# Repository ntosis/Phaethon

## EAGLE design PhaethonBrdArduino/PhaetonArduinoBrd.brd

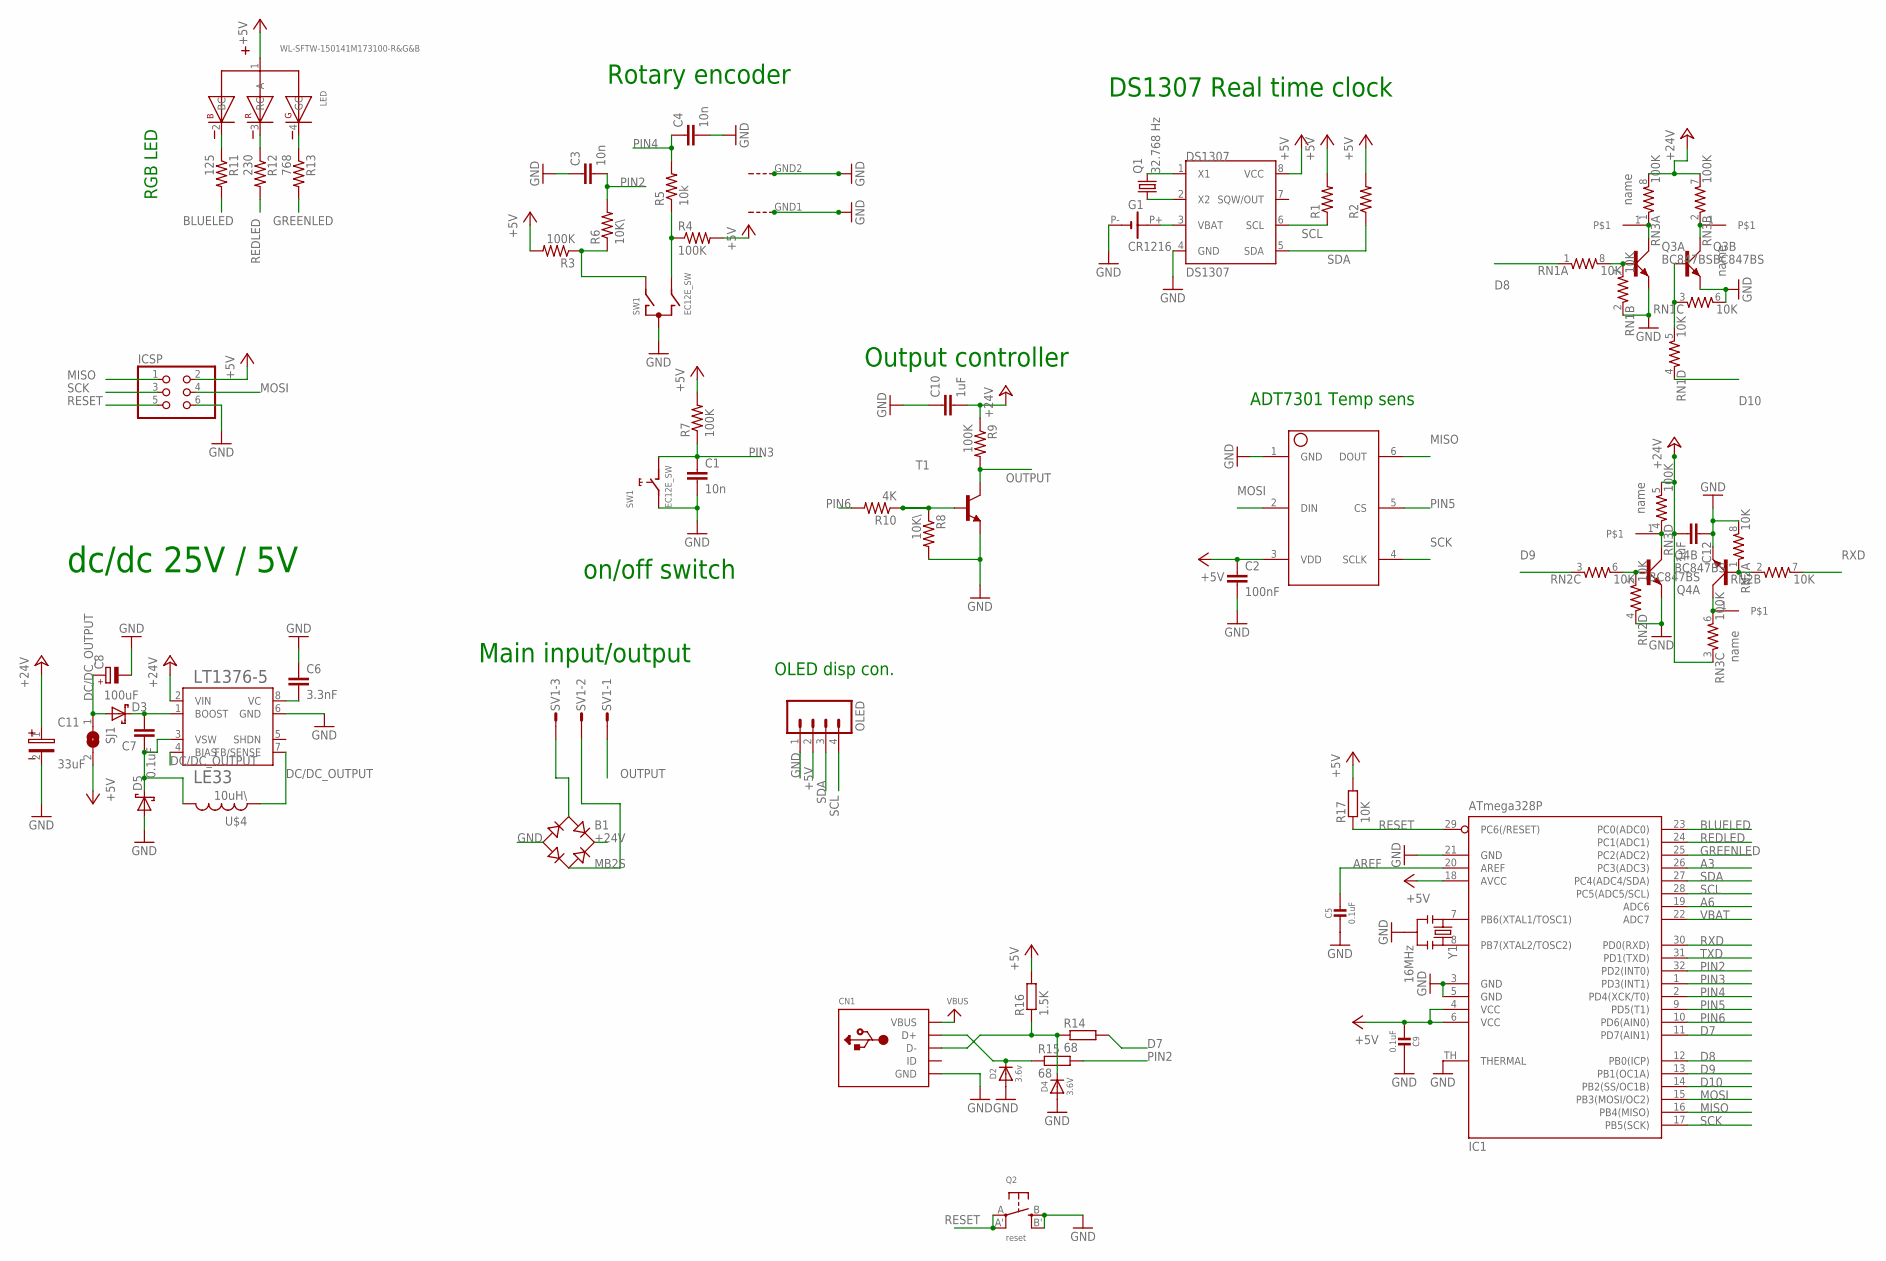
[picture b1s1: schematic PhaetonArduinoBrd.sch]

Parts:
ADT: ADT7301; SOT23-6
B1: MB2S; SOIC-4
C1, C3, C4: 10n; C0504
C2: 100nF; C0504
C5, C9: 0.1uF; _0805MP
C6: 3.3nF; C0504
C7: 0.1uF; C0504
C8: 100uF; CT7343
C10, C12: 1uF; C0402
C11: 33uF; 3X1.6X1.4(BXCXA)
CN1: USBMINIB; USB-MINIB
D2: 3.6v; SOD-323
D3, D5: SCHOTTKY; DO214
D4: 3.6V; SOD-323
DS1307: DS1307; SOIC-8
G1: CR1216; SMTU1225-LF
IC1: ATmega328P; MLF32-TH
ICSP: PINHD-2X3; 2X03
LED: WL-SFTW-150141M173100-R&G&B; 3528-COMMON-ANODE
LT1376-5: LE33; SO08
OLED: M04; 04P
OUTPUT2: MINICONECTOR; SMD
Q1: 32.768 Hz; TC26V
Q2: reset; BTN_KMR2_4.6X2.8
Q3, Q4: BC847BS; SOT363_PHILIPS
R1, R2: RESISTOR; 0805
R3, R4, R7, R9: 100K; 0805
R5: 10k; 0805
R6, R8: 10K\; 0805
R10: 4K; 0805
R11: 125; 0805
R12: 230; 0805
R13: 768; 0805
R14, R15: 68; R0603
R16: 1.5K; R0603
R17: 10K; R0603
RN1, RN2: 10K; 741-8
RN3: 100K; 741-8
SJ1: SJ
SV1: MT6-3
SW1: EC12E_SW; ALPS_EC12E_SW
T1: BC818-16-NPN-SOT23-BEC; SOT23-BEC
U$3, U$5, U$6: MINICONECTOR; SMD
U$4: 10uH\; 103MRB
Y1: 16MHz; RESONATOR-SMD

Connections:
+5V: ADT.3 (VDD), C2.1, C9.2, DS1307.8 (VCC), IC1.4 (VCC), IC1.6 (VCC), IC1.18 (AVCC), ICSP.2, LED.1 (A), OLED.2, R1.2, R2.2, R3.2, R4.2, R7.2, R16.2, R17.2, SJ1.2
+24V: B1.+, C10.2, C11.1, C12.2, LT1376-5.2 (VIN), R9.1, RN3.3 (1), RN3.5 (2), RN3.7 (2), RN3.8 (2)
A3: IC1.26 (PC3(ADC3))
A6: IC1.19 (ADC6)
AREF: C5.1, IC1.20 (AREF)
BLUELED: IC1.23 (PC0(ADC0)), R11.2
D7: IC1.11 (PD7(AIN1)), R14.2
D8: IC1.12 (PB0(ICP)), RN1.1
D9: IC1.13 (PB1(OC1A)), RN2.3 (1)
D10: IC1.14 (PB2(SS/OC1B)), RN1.4 (1)
D+: CN1.D+, D2.C, R15.1
D-: CN1.D-, D4.C, R14.1, R16.1
DC/DC_OUTPUT: C8.+, D3.A, LT1376-5.4 (BIAS), LT1376-5.7 (FB/SENSE), SJ1.1, U$4.2
GND: ADT.1 (GND), B1.-, C1.2, C2.2, C3.1, C4.2, C5.2, C6.1, C8.-, C9.1, C10.1, C11.2, C12.1, CN1.GND, D2.A, D4.A, D5.A, DS1307.4 (GND), G1.P- (-), IC1.3 (GND), IC1.5 (GND), IC1.21 (GND), IC1.TH (THERMAL), ICSP.6, LT1376-5.6 (GND), OLED.1, Q2.B (S), Q2.B' (S1), Q3.1 (E), Q3.4 (E), Q4.1 (E), Q4.4 (E), R8.2, RN1.2 (1), RN1.6 (2), RN2.4 (1), RN2.8 (2), SW1.C, SW1.E (2), SW1.GND1 (G), SW1.GND2 (G), T1.E, Y1.2
GREENLED: IC1.25 (PC2(ADC2)), R13.2
MISO: ADT.6 (DOUT), IC1.16 (PB4(MISO)), ICSP.1
MOSI: ADT.2 (DIN), IC1.15 (PB3(MOSI/OC2)), ICSP.4
unnamed: LED.2 (BC), R11.1
unnamed: LED.3 (RC), R12.1
unnamed: LED.4 (GC), R13.1
unnamed: B1.~1 (AC1), SV1.3
unnamed: DS1307.2 (X2), Q1.1
unnamed: B1.~2 (AC2), SV1.2
unnamed: IC1.8 (PB7(XTAL2/TOSC2)), Y1.3
unnamed: IC1.7 (PB6(XTAL1/TOSC1)), Y1.1
unnamed: R8.1, R10.1, T1.B
unnamed: OUTPUT2.1, Q3.6 (C), RN3.1
unnamed: C6.2, LT1376-5.8 (VC)
unnamed: C7.2, D3.C, LT1376-5.1 (BOOST)
unnamed: Q3.3 (C), RN3.2 (1), U$3.1
unnamed: C7.1, D5.C, LT1376-5.3 (VSW), U$4.1
unnamed: Q4.2 (B), RN2.1, RN2.2 (1)
unnamed: Q3.2 (B), RN1.7 (2), RN1.8 (2)
unnamed: Q3.5 (B), RN1.3 (1), RN1.5 (2)
unnamed: Q4.5 (B), RN2.5 (2), RN2.6 (2)
unnamed: Q4.3 (C), RN3.4 (1), U$6.1
unnamed: Q4.6 (C), RN3.6 (2), U$5.1
unnamed: R3.1, R6.1, SW1.A
unnamed: R4.1, R5.1, SW1.B
unnamed: DS1307.1 (X1), Q1.2
OUTPUT: R9.2, SV1.1, T1.C
PIN2: C3.2, IC1.32 (PD2(INT0)), R6.2, R15.2
PIN3: C1.1, IC1.1 (PD3(INT1)), R7.1, SW1.D (1)
PIN4: C4.1, IC1.2 (PD4(XCK/T0)), R5.2
PIN5: ADT.5 (CS), IC1.9 (PD5(T1))
PIN6: IC1.10 (PD6(AIN0)), R10.2
REDLED: IC1.24 (PC1(ADC1)), R12.2
RESET: IC1.29 (PC6(/RESET)), ICSP.5, Q2.A, Q2.A' (P1), R17.1
RXD: IC1.30 (PD0(RXD)), RN2.7 (2)
SCK: ADT.4 (SCLK), IC1.17 (PB5(SCK)), ICSP.3
SCL: DS1307.6 (SCL), IC1.28 (PC5(ADC5/SCL)), OLED.4, R1.1
SDA: DS1307.5 (SDA), IC1.27 (PC4(ADC4/SDA)), OLED.3, R2.1
SHDN: LT1376-5.5 (SHDN)
TXD: IC1.31 (PD1(TXD))
VBAT: DS1307.3 (VBAT), G1.P+ (+), IC1.22 (ADC7)
VBUS: CN1.VBUS

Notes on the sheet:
Rotary encoder
DS1307 Real time clock
RGB LED
on/off switch
Main input/output
OLED disp con.
Output controller
ADT7301 Temp sens
dc/dc 25V / 5V

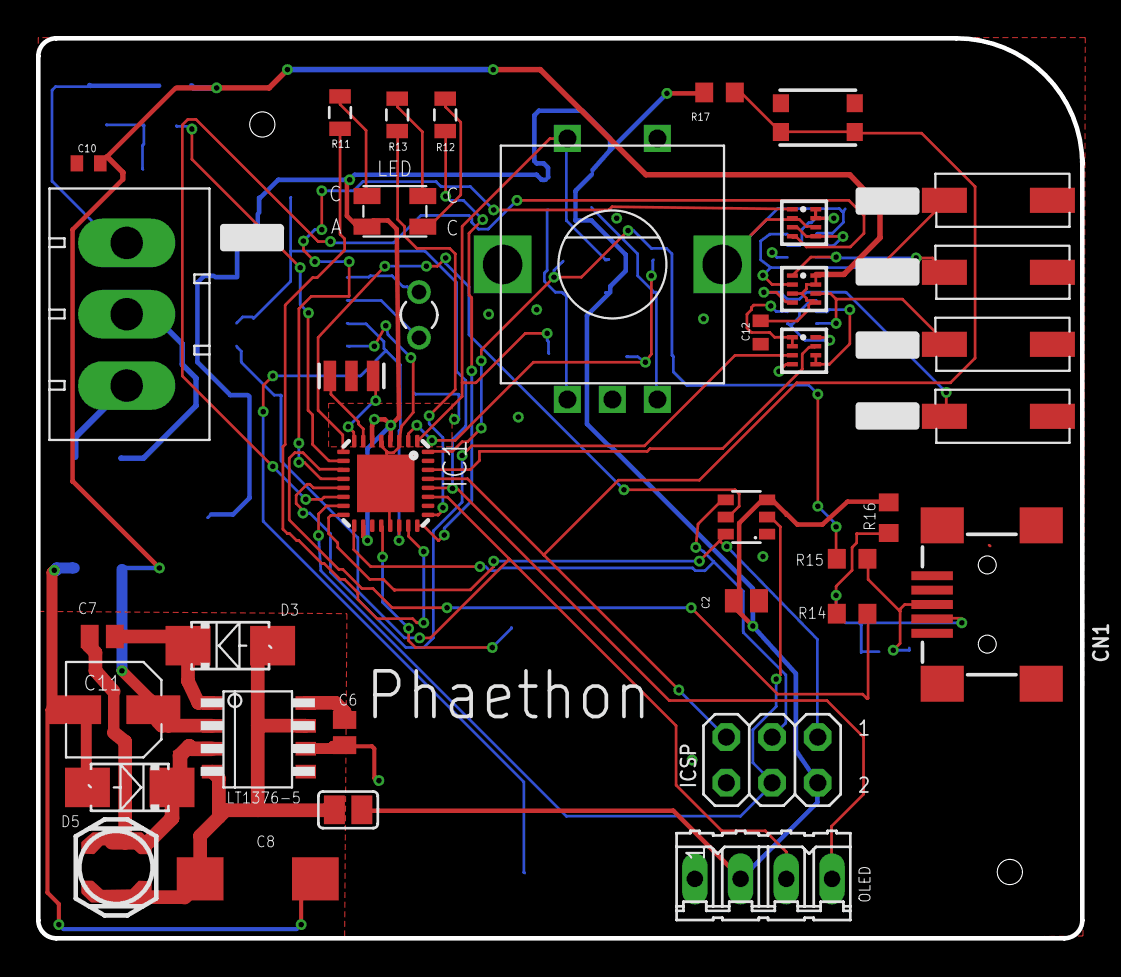
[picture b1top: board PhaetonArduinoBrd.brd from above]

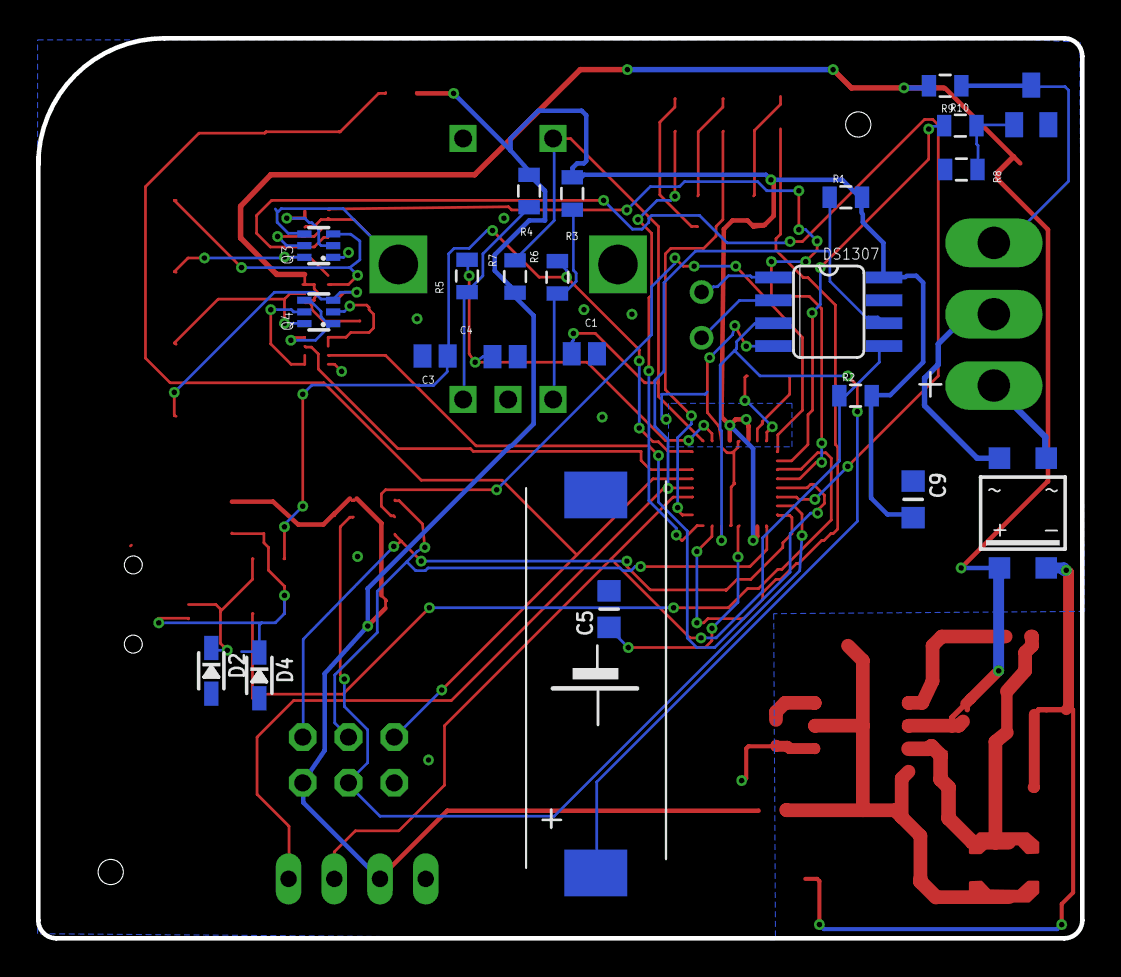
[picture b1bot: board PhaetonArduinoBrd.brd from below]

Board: 2 copper layers, 58.0 x 50.0 mm, 60 parts (23 on the bottom side), 51 nets.

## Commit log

2015-11-14 added comments
2015-11-15 Initial creation of the files for Arduino shield
2015-11-28 initial commit for the AVR Atmega 168 core
2015-11-28 removed wrong file
2015-11-28 added eclipse project files
2015-11-28 deleted files that are not for this branch
2015-11-28 added the Hex file and etc.
2015-12-04 Schematic updated
2015-12-04 removed unusable and old comments
2015-12-04 Debugging command removed
2015-12-04 removed from board unusable vias
2015-12-05 added labels for every component
2015-12-05 updated include path for my local PC
2015-12-07 Bug fixed with Automatic program
2015-12-08 Updated schematic and first board is designed
2015-12-09 Bug fixed, Temperature sens was not connected
2015-12-09 i hope final layout before seed studio
2015-12-12 a lot of bug fixes
2015-12-12 Bug fixed: When the thermostat was off the control pin was not in HIGH state, so the heating system was always on
2015-12-14 changed the times for the tasks
2015-12-14 Bug fixed: when are the software back to manual program from autoprogram, didnt work correctly the manual function.
2015-12-14 ichanged the hours to passed my personal program, nothing importand
2015-12-17 Initial files for OLED Display
2015-12-17 Changes for OLED display compatibility
2015-12-18 Display debug messages added
2015-12-18 Bug fixed, when a task needs more than 100ms then the 'task_list[i].delay was negative,the task couldnt be runnable again'
2015-12-18 More debug infos at OLED
2015-12-19 rtc chip migrated to the new i2c lib
2015-12-19 Paths updated
2015-12-19 when the PID controller is off, software sets to zero the Integrator
2015-12-19 removed obsolote lib
2016-01-16 Added more debug infos on the display's message.
2016-01-16 Issue: Change the RGB LED #1
2016-01-24 Change the PID code. Issue #4
2016-01-24 Removed unusual comments.
2016-01-24 adafa
2016-01-26 Add all the ports definitions in pinmacros.h #6
2016-01-30 Development branch, add new function, so the user could set date/time.
2016-02-09 Set the date function added.
2016-02-10 The chip select pin moved into pinmacros header.
2016-02-10 RED_LED pin is renamed to a more usual name. All tasks in main are enabled.
2016-02-10 Added a write to register of the ds1307 for the seconds, and when the user set the time the defaults values are not equal to zero.
2016-02-13 Tm1637 pins defines moved to pinmacros header.
2016-02-16 Added new function to show the Soll temperature during the change.
2016-02-20 PID tuned try.
2016-02-24 Added bridge, Issue #3
2016-02-28 Nes software design which based on Matlab 2014 model.
2016-03-12 New design, before Checks
2016-03-15 Phaethon V2 in Seedstudio
2016-03-20 *To be tested if with the new change in CheckStruct,reseting the variable pnt;, the Button function is more reliable. *The struct for the click is now an Array and not need to allocated with malloc()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
2016-06-07 "Led code changed to be compatible with new board."
2016-06-07 Boundary checks updated and configured to work properly.
2016-06-10 LED function optimized for the new LED.
2016-06-10 #7 DS1307 lib can set also the time and the date, additionally we added boundary checks for the arrays.
2016-07-03 removed tm1637 folder
2016-07-07 renamed base folder
2016-07-07 added the eeprom module to store calibrations variables.
2016-07-11 Added Calibration parameters and they are in EEprom.
2016-07-11 Share the char buf array from the main.c, we use 80 bytes less ram.
2016-07-11 Use sprintf_P() function to read strings from Flash. More RAM memory available to use for other components.
2016-07-13 Heating and Cooling System is added but not tested.
2016-07-30 Added Graphics for heating and cooling function.
2016-07-30 Added graphics for heating cooling function.
2016-07-30 added comment
2016-07-30 Added the compilers output files.
2016-07-30 added and removed files from version control
2016-08-11 Added function to spring quickly from heating to cooling.

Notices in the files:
parts and their libraries:
Wuerth_Elektronik_LEDs_rev15b: Copyright: Würth Elektronik
microbuilder: This work is placed in the public domain, and may be freely used for commercial and non-commercial work with the following conditions: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
resistor-array: Copyright (C) 2008, Bob Starr
